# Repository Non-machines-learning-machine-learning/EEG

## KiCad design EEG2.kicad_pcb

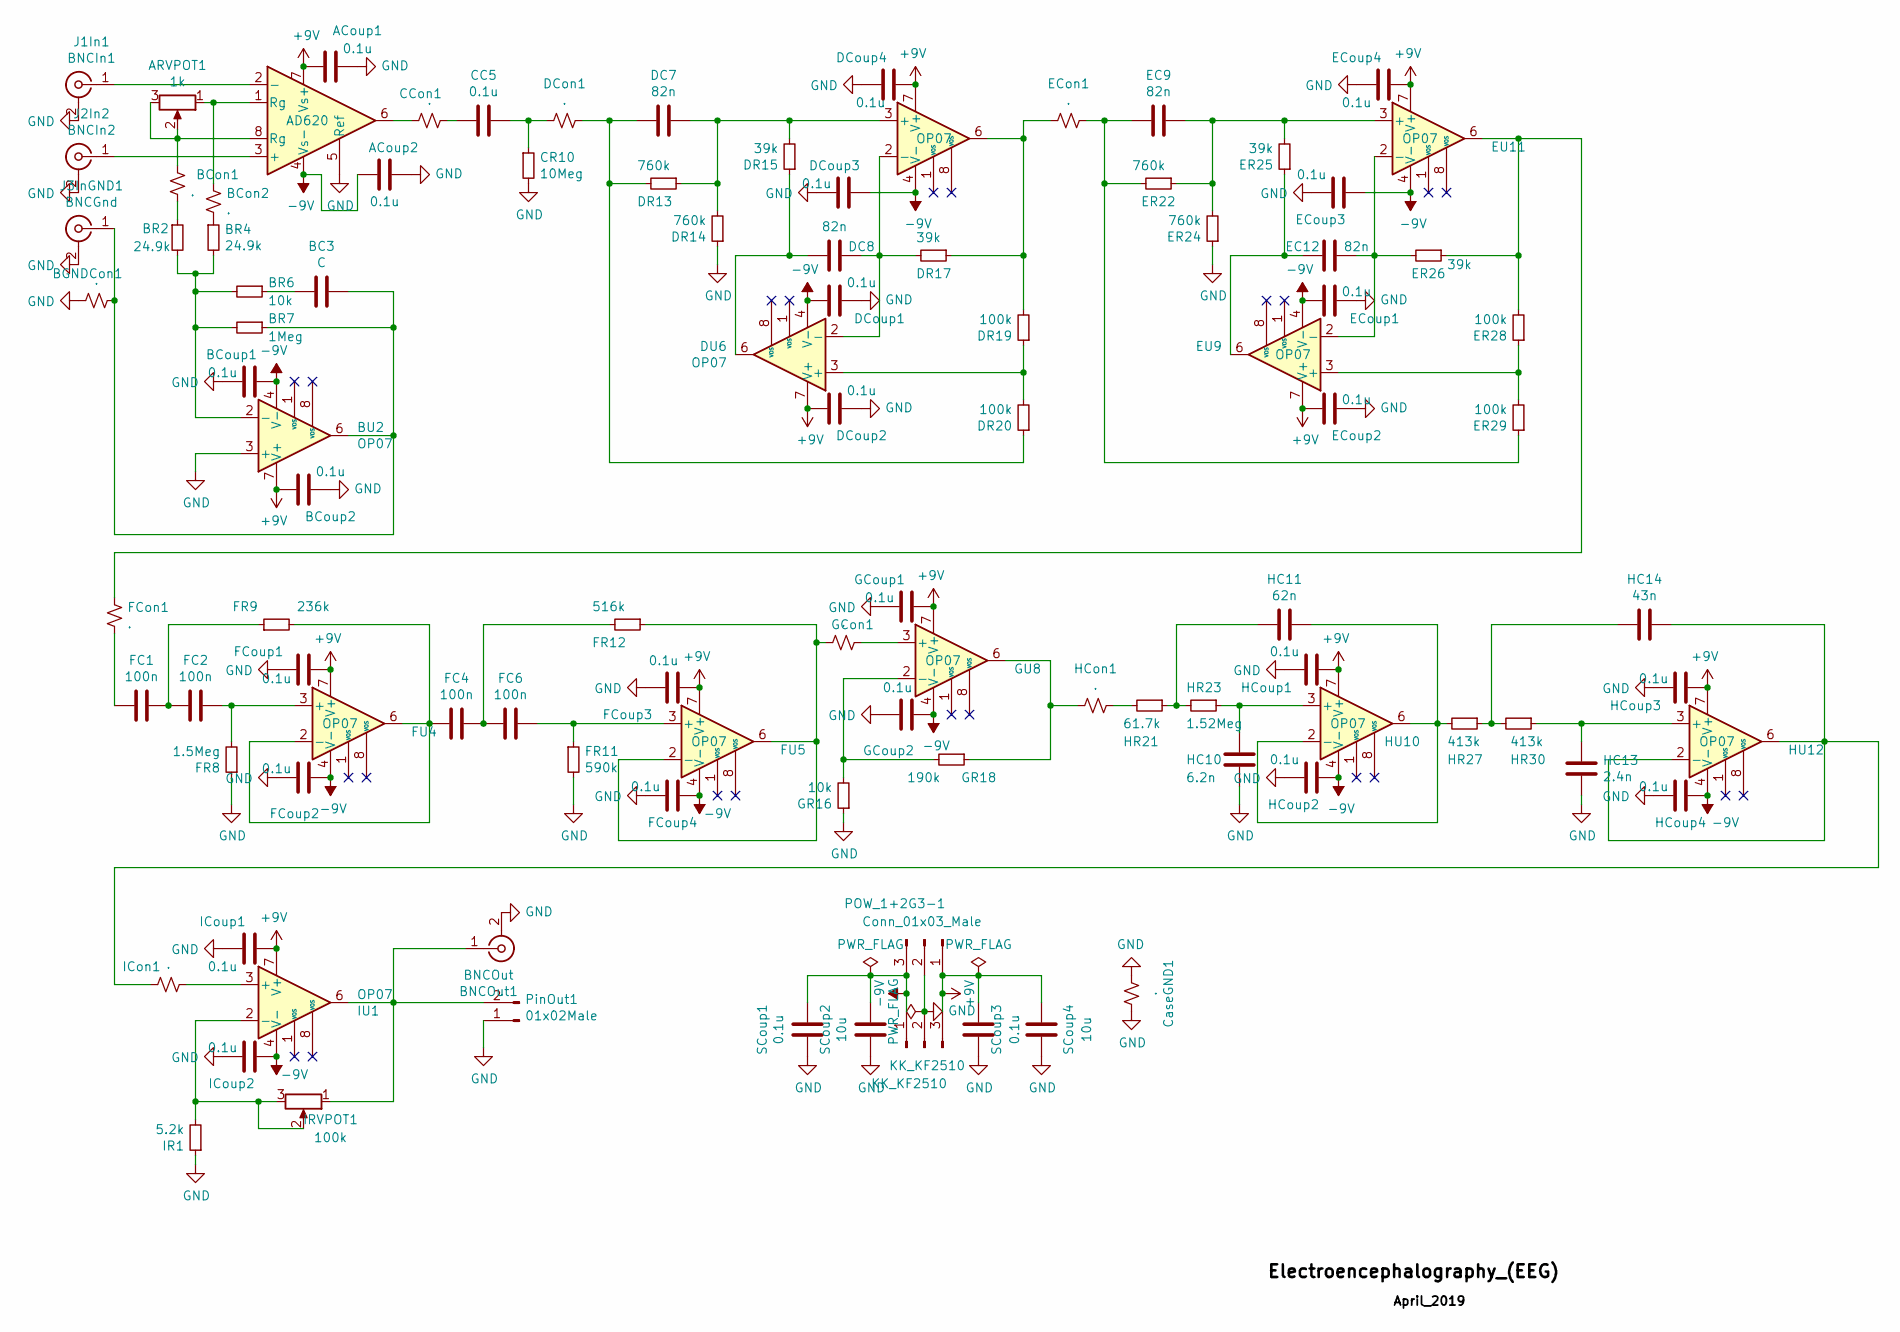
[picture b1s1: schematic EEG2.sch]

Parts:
ACoup1, ACoup2: 0.1u; C_Disc_D5.0mm_W2.5mm_P2.50mm
ARVPOT1: 1k; Potentiometer_Bourns_3386P_Vertical
AU3: AD620; DIP-8_W7.62mm
BC3: C; C_Radial_D10.0mm_H12.5mm_P5.00mm
BCon1, BCon2: .; R_Axial_DIN0207_L6.3mm_D2.5mm_P10.16mm_Horizontal
BCoup1, BCoup2: 0.1u; C_Disc_D5.0mm_W2.5mm_P2.50mm
BGNDCon1: .; R_Axial_DIN0207_L6.3mm_D2.5mm_P10.16mm_Horizontal
BNCOut1: BNCOut; BNC_Amphenol_B6252HB-NPP3G-50_Horizontal
BR2, BR4: 24.9k; R_Axial_DIN0207_L6.3mm_D2.5mm_P10.16mm_Horizontal
BR6: 10k; R_Axial_DIN0207_L6.3mm_D2.5mm_P10.16mm_Horizontal
BR7: 1Meg; R_Axial_DIN0207_L6.3mm_D2.5mm_P10.16mm_Horizontal
BU2: OP07; DIP-8_W7.62mm
CC5: 0.1u; C_Disc_D5.0mm_W2.5mm_P2.50mm
CCon1: .; R_Axial_DIN0207_L6.3mm_D2.5mm_P10.16mm_Horizontal
CR10: 10Meg; R_Axial_DIN0207_L6.3mm_D2.5mm_P10.16mm_Horizontal
CaseGND1: .; R_Axial_DIN0207_L6.3mm_D2.5mm_P10.16mm_Horizontal
DC7, DC8: 82n; C_Disc_D7.5mm_W5.0mm_P7.50mm
DCon1: .; R_Axial_DIN0207_L6.3mm_D2.5mm_P10.16mm_Horizontal
DCoup1, DCoup2, DCoup3, DCoup4: 0.1u; C_Disc_D5.0mm_W2.5mm_P2.50mm
DR13, DR14: 760k; R_Axial_DIN0207_L6.3mm_D2.5mm_P10.16mm_Horizontal
DR15, DR17: 39k; R_Axial_DIN0207_L6.3mm_D2.5mm_P10.16mm_Horizontal
DR19, DR20: 100k; R_Axial_DIN0207_L6.3mm_D2.5mm_P10.16mm_Horizontal
DU6, DU7: OP07; DIP-8_W7.62mm
EC9, EC12: 82n; C_Disc_D7.5mm_W5.0mm_P7.50mm
ECon1: .; R_Axial_DIN0207_L6.3mm_D2.5mm_P10.16mm_Horizontal
ECoup1, ECoup2, ECoup3, ECoup4: 0.1u; C_Disc_D5.0mm_W2.5mm_P2.50mm
ER22, ER24: 760k; R_Axial_DIN0207_L6.3mm_D2.5mm_P10.16mm_Horizontal
ER25, ER26: 39k; R_Axial_DIN0207_L6.3mm_D2.5mm_P10.16mm_Horizontal
ER28, ER29: 100k; R_Axial_DIN0207_L6.3mm_D2.5mm_P10.16mm_Horizontal
EU9, EU11: OP07; DIP-8_W7.62mm
FC1: 100n; C_Disc_D5.0mm_W2.5mm_P2.50mm
FC2, FC4, FC6: 100n; C_Disc_D3.0mm_W1.6mm_P2.50mm
FCon1: .; R_Axial_DIN0207_L6.3mm_D2.5mm_P10.16mm_Horizontal
FCoup1, FCoup2, FCoup3, FCoup4: 0.1u; C_Disc_D5.0mm_W2.5mm_P2.50mm
FR8: 1.5Meg; R_Axial_DIN0207_L6.3mm_D2.5mm_P10.16mm_Horizontal
FR9: 236k; R_Axial_DIN0207_L6.3mm_D2.5mm_P10.16mm_Horizontal
FR11: 590k; R_Axial_DIN0207_L6.3mm_D2.5mm_P10.16mm_Horizontal
FR12: 516k; R_Axial_DIN0207_L6.3mm_D2.5mm_P10.16mm_Horizontal
FU4, FU5: OP07; DIP-8_W7.62mm
GCon1: .; R_Axial_DIN0207_L6.3mm_D2.5mm_P10.16mm_Horizontal
GCoup1, GCoup2: 0.1u; C_Disc_D5.0mm_W2.5mm_P2.50mm
GR16: 10k; R_Axial_DIN0207_L6.3mm_D2.5mm_P10.16mm_Horizontal
GR18: 190k; R_Axial_DIN0207_L6.3mm_D2.5mm_P10.16mm_Horizontal
GU8: OP07; DIP-8_W7.62mm
HC10: 6.2n; C_Disc_D7.5mm_W4.4mm_P5.00mm
HC11: 62n; C_Disc_D7.5mm_W5.0mm_P10.00mm
HC13: 2.4n; C_Disc_D5.1mm_W3.2mm_P5.00mm
HC14: 43n; C_Disc_D3.8mm_W2.6mm_P2.50mm
HCon1: .; R_Axial_DIN0207_L6.3mm_D2.5mm_P10.16mm_Horizontal
HCoup1, HCoup2, HCoup3, HCoup4: 0.1u; C_Disc_D5.0mm_W2.5mm_P2.50mm
HR21: 61.7k; R_Axial_DIN0207_L6.3mm_D2.5mm_P10.16mm_Horizontal
HR23: 1.52Meg; R_Axial_DIN0207_L6.3mm_D2.5mm_P10.16mm_Horizontal
HR27, HR30: 413k; R_Axial_DIN0207_L6.3mm_D2.5mm_P10.16mm_Horizontal
HU10, HU12: OP07; DIP-8_W7.62mm
ICon1: .; R_Axial_DIN0207_L6.3mm_D2.5mm_P10.16mm_Horizontal
ICoup1, ICoup2: 0.1u; C_Disc_D5.0mm_W2.5mm_P2.50mm
IR1: 5.2k; R_Axial_DIN0207_L6.3mm_D2.5mm_P10.16mm_Horizontal
IRVPOT1: 100k; Potentiometer_Bourns_3386P_Vertical
IU1: OP07; DIP-8_W7.62mm
J1In1: BNCIn1; BNC_Amphenol_B6252HB-NPP3G-50_Horizontal
J2In2: BNCIn2; BNC_Amphenol_B6252HB-NPP3G-50_Horizontal
J3InGND1: BNCGnd; BNC_Amphenol_B6252HB-NPP3G-50_Horizontal
KK_KF2510: KK_KF2510; Molex_KK-254_AE-6410-03A_1x03_P2.54mm_Vertical
POW_1+2G3-1: Conn_01x03_Male; PinHeader_1x03_P2.54mm_Vertical
PinOut1: 01x02Male; PinHeader_1x02_P2.54mm_Vertical
SCoup1, SCoup3: 0.1u; C_Disc_D5.0mm_W2.5mm_P2.50mm
SCoup2, SCoup4: 10u; C_Radial_D10.0mm_H12.5mm_P5.00mm

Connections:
+9V: ACoup1.2, AU3.7 (Vs+), BCoup2.2, BU2.7 (V+), DCoup2.2, DCoup4.2, DU6.7 (V+), DU7.7 (V+), ECoup2.1, ECoup4.2, EU9.7 (V+), EU11.7 (V+), FCoup1.2, FCoup3.2, FU4.7 (V+), FU5.7 (V+), GCoup1.2, GU8.7 (V+), HCoup1.2, HCoup3.2, HU10.7 (V+), HU12.7 (V+), ICoup1.2, IU1.7 (V+), KK_KF2510.3, POW_1+2G3-1.1, SCoup3.1, SCoup4.1; also elsewhere on the board
-9V: ACoup2.2, AU3.4 (Vs-), BCoup1.1, BU2.4 (V-), DCoup1.2, DCoup3.2, DU6.4 (V-), DU7.4 (V-), ECoup1.1, ECoup3.2, EU9.4 (V-), EU11.4 (V-), FCoup2.2, FCoup4.2, FU4.4 (V-), FU5.4 (V-), GCoup2.2, GU8.4 (V-), HCoup2.2, HCoup4.2, HU10.4 (V-), HU12.4 (V-), ICoup2.2, IU1.4 (V-), KK_KF2510.1, POW_1+2G3-1.3, SCoup1.1, SCoup2.1; also elsewhere on the board
GND: ACoup1.1, ACoup2.1, AU3.5 (Ref), BCoup1.2, BCoup2.1, BGNDCon1.2, BNCOut1.2 (Ext), BU2.3 (+), CR10.2, CaseGND1.1, CaseGND1.2, DCoup1.1, DCoup2.1, DCoup3.1, DCoup4.1, DR14.1, ECoup1.2, ECoup2.2, ECoup3.1, ECoup4.1, ER24.1, FCoup1.1, FCoup2.1, FCoup3.1, FCoup4.1, FR8.1, FR11.2, GCoup1.1, GCoup2.1, GR16.1, HC10.1, HC13.1, HCoup1.1, HCoup2.1, HCoup3.1, HCoup4.1, ICoup1.1, ICoup2.1, IR1.1, J1In1.2 (Ext), J2In2.2 (Ext), J3InGND1.2 (Ext), KK_KF2510.2, POW_1+2G3-1.2, PinOut1.1, SCoup1.2, SCoup2.2, SCoup3.2, SCoup4.2; also elsewhere on the board
unnamed: ARVPOT1.1, AU3.1 (Rg), BCon2.2
unnamed: ARVPOT1.2, ARVPOT1.3, AU3.8 (Rg), BCon1.2
unnamed: AU3.2 (-), J1In1.1 (In)
unnamed: AU3.3 (+), J2In2.1 (In)
unnamed: AU3.6, CCon1.2
unnamed: BC3.1, BGNDCon1.1, BR7.1, BU2.6, J3InGND1.1 (In)
unnamed: BC3.2, BR6.1
unnamed: BCon1.1, BR2.1
unnamed: BCon2.1, BR4.1
unnamed: BNCOut1.1 (In), IRVPOT1.1, IU1.6, PinOut1.2
unnamed: BR2.2, BR4.2, BR6.2, BR7.2, BU2.2 (-)
unnamed: CC5.1, CR10.1, DCon1.2
unnamed: CC5.2, CCon1.1
unnamed: DC7.1, DR13.1, DR14.2, DR15.2, DU7.3 (+)
unnamed: DC7.2, DCon1.1, DR13.2, DR20.1
unnamed: DC8.1, DR15.1, DU6.6
unnamed: DC8.2, DR17.2, DU6.2 (-), DU7.2 (-)
unnamed: DR17.1, DR19.2, DU7.6, ECon1.2
unnamed: DR19.1, DR20.2, DU6.3 (+)
unnamed: EC9.1, ER22.1, ER24.2, ER25.2, EU11.3 (+)
unnamed: EC9.2, ECon1.1, ER22.2, ER29.1
unnamed: EC12.1, ER25.1, EU9.6
unnamed: EC12.2, ER26.2, EU9.2 (-), EU11.2 (-)
unnamed: ER26.1, ER28.2, EU11.6, FCon1.2
unnamed: ER28.1, ER29.2, EU9.3 (+)
unnamed: FC1.1, FC2.2, FR9.1
unnamed: FC1.2, FCon1.1
unnamed: FC2.1, FR8.2, FU4.3 (+)
unnamed: FC4.1, FC6.2, FR12.2
unnamed: FC4.2, FR9.2, FU4.2 (-), FU4.6
unnamed: FC6.1, FR11.1, FU5.3 (+)
unnamed: FR12.1, FU5.2 (-), FU5.6, GCon1.1
unnamed: GCon1.2, GU8.3 (+)
unnamed: GR16.2, GR18.2, GU8.2 (-)
unnamed: GR18.1, GU8.6, HCon1.1
unnamed: HC10.2, HR23.1, HU10.3 (+)
unnamed: HC11.1, HR27.2, HU10.2 (-), HU10.6
unnamed: HC11.2, HR21.1, HR23.2
unnamed: HC13.2, HR30.1, HU12.3 (+)
unnamed: HC14.1, HR27.1, HR30.2
unnamed: HC14.2, HU12.2 (-), HU12.6, ICon1.1
unnamed: HCon1.2, HR21.2
unnamed: ICon1.2, IU1.3 (+)
unnamed: IR1.2, IRVPOT1.2, IRVPOT1.3, IU1.2 (-)

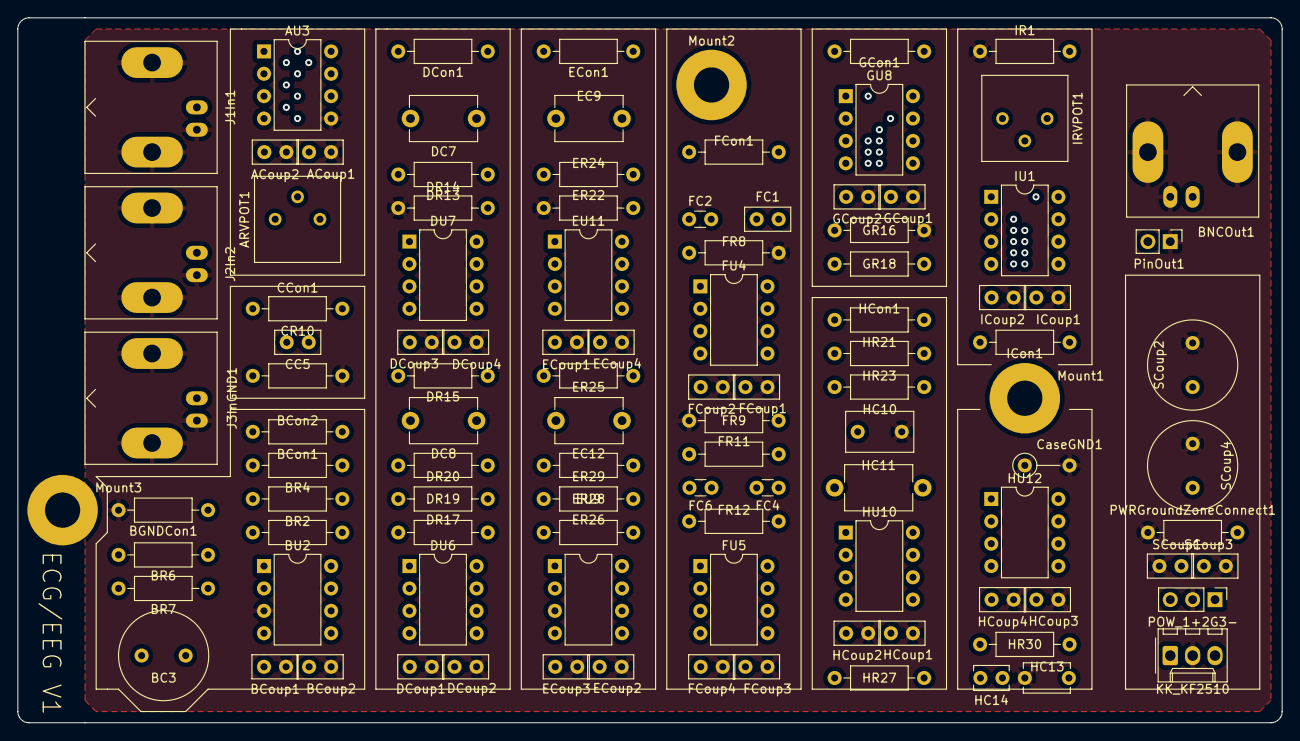
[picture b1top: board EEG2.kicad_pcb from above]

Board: 4 copper layers, 143.5 x 80.0 mm, 106 parts (0 on the bottom side), 47 nets.

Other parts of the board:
Mount1, Mount2, Mount3: MountingHole_4mm_Pad
POW_1+2G3-: Conn_01x03_Male; PinHeader_1x03_P2.54mm_Vertical
PWRGroundZoneConnect1: 0; R_Axial_DIN0207_L6.3mm_D2.5mm_P10.16mm_Horizontal

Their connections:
+9V: POW_1+2G3-.1; also elsewhere on the board
-9V: POW_1+2G3-.3; also elsewhere on the board
GND: POW_1+2G3-.2, PWRGroundZoneConnect1.1; also elsewhere on the board

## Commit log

2019-07-07 dan cant github
